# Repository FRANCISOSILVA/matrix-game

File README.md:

# Matrix-Game

Copyright (C) 2025 GWF AG, Obergrundstrasse 119, 6002 Lucerne, Switzerland

Contact: info@gwf.ch

## Trial Apprenticeship

This PCB is used as part of the trial apprenticeship for electronics/firmware at GWF AG in Lucerne.

_Deutsch: Schnupperlehre Elektroniker/in EFZ_

## Project

The project is used to practice soldering, measuring and potentially some coding.

The firmware currently supports the following games:
- [x] Snake
- [x] Tic-Tac-Toe

Feel free to submit a Pull Request to add more games! :tada:

## Changelogs

The changelogs can be find in the corresponding subdirectories:
- [Firmware Changelog](firmware/CHANGELOG.md)
- [Hardware Changelog](hardware/CHANGELOG.md)

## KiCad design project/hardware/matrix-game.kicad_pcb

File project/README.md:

# Project: Matrix-Game

This PCB is used as part of the trial apprenticeship to practice soldering, measuring and potentially some coding.

The firmware currently supports the following games:
- [x] Snake
- [x] Tic-Tac-Toe

Feel free to submit a Pull Request to add more games! :tada:

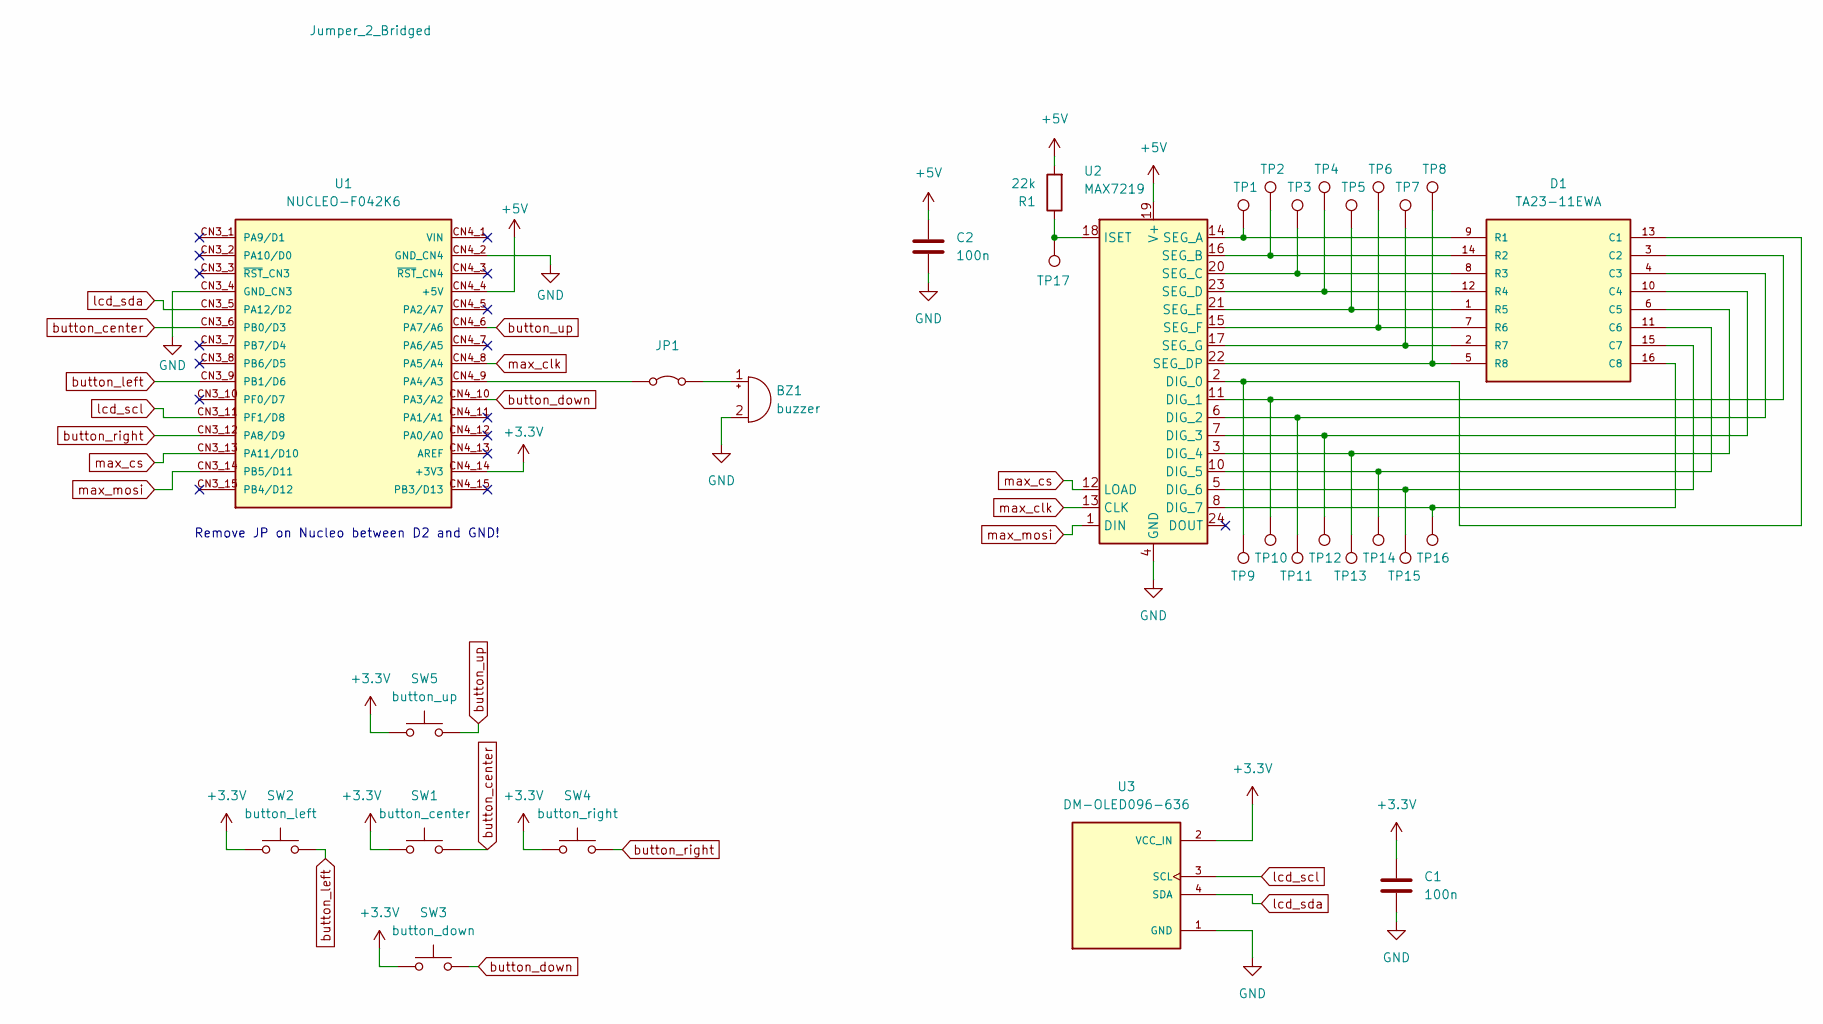
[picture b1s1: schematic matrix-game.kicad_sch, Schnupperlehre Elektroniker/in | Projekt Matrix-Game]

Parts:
BZ1: buzzer; Buzzer_12x9.5RM7.6
C1, C2: 100n; C_Disc_D3.0mm_W2.0mm_P2.50mm
D1: TA23-11EWA; LED_TA23-11EWA; PARTREV V.10A
JP1: Jumper_2_Bridged; PinHeader_1x02_P2.54mm_Vertical
R1: 22k; R_Axial_DIN0207_L6.3mm_D2.5mm_P10.16mm_Horizontal
SW1: button_center; SW_PUSH_6mm
SW2: button_left; SW_PUSH_6mm
SW3: button_down; SW_PUSH_6mm
SW4: button_right; SW_PUSH_6mm
SW5: button_up; SW_PUSH_6mm
TP1, TP2, TP3, TP4, TP5, TP6, TP7, TP8, TP9, TP10, TP11, TP12, TP13, TP14, TP15, TP16, TP17: TestPoint; PinHeader_1x01_P2.54mm_Vertical
U1: NUCLEO-F042K6; MODULE_NUCLEO-F042K6; PARTREV 8
U2: MAX7219; DIP-24_W7.62mm_Socket
U3: DM-OLED096-636; MODULE_DM-OLED096-636; PARTREV 2018-09-10

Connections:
+3.3V: C1.1, SW1.1, SW2.1, SW3.1, SW4.1, SW5.1, U1.CN4_14 (+3V3), U3.2 (VCC_IN)
+5V: C2.1, R1.2, U1.CN4_4 (+5V), U2.19 (V+)
GND: BZ1.2 (-), C1.2, C2.2, U1.CN3_4 (GND_CN3), U1.CN4_2 (GND_CN4), U2.4 (GND), U2.9 (GND), U3.1 (GND)
unnamed: BZ1.1 (+), JP1.2 (B)
unnamed: D1.13 (C1), TP9.1, U2.2 (DIG_0)
unnamed: D1.3 (C2), TP10.1, U2.11 (DIG_1)
unnamed: D1.4 (C3), TP11.1, U2.6 (DIG_2)
unnamed: D1.10 (C4), TP12.1, U2.7 (DIG_3)
unnamed: D1.6 (C5), TP13.1, U2.3 (DIG_4)
unnamed: D1.11 (C6), TP14.1, U2.10 (DIG_5)
unnamed: D1.15 (C7), TP15.1, U2.5 (DIG_6)
unnamed: D1.16 (C8), TP16.1, U2.8 (DIG_7)
unnamed: D1.9 (R1), TP1.1, U2.14 (SEG_A)
unnamed: D1.14 (R2), TP2.1, U2.16 (SEG_B)
unnamed: D1.8 (R3), TP3.1, U2.20 (SEG_C)
unnamed: D1.12 (R4), TP4.1, U2.23 (SEG_D)
unnamed: D1.1 (R5), TP5.1, U2.21 (SEG_E)
unnamed: D1.7 (R6), TP6.1, U2.15 (SEG_F)
unnamed: D1.2 (R7), TP7.1, U2.17 (SEG_G)
unnamed: D1.5 (R8), TP8.1, U2.22 (SEG_DP)
unnamed: JP1.1 (A), U1.CN4_9 (PA4/A3)
unnamed: R1.1, TP17.1, U2.18 (ISET)
button_center: SW1.2, U1.CN3_6 (PB0/D3)
button_down: SW3.2, U1.CN4_10 (PA3/A2)
button_left: SW2.2, U1.CN3_9 (PB1/D6)
button_right: SW4.2, U1.CN3_12 (PA8/D9)
button_up: SW5.2, U1.CN4_6 (PA7/A6)
lcd_scl: U1.CN3_11 (PF1/D8), U3.3 (SCL)
lcd_sda: U1.CN3_5 (PA12/D2), U3.4 (SDA)
max_clk: U1.CN4_8 (PA5/A4), U2.13 (CLK)
max_cs: U1.CN3_13 (PA11/D10), U2.12 (LOAD)
max_mosi: U1.CN3_14 (PB5/D11), U2.1 (DIN)

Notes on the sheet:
Remove JP on Nucleo between D2 and GND!

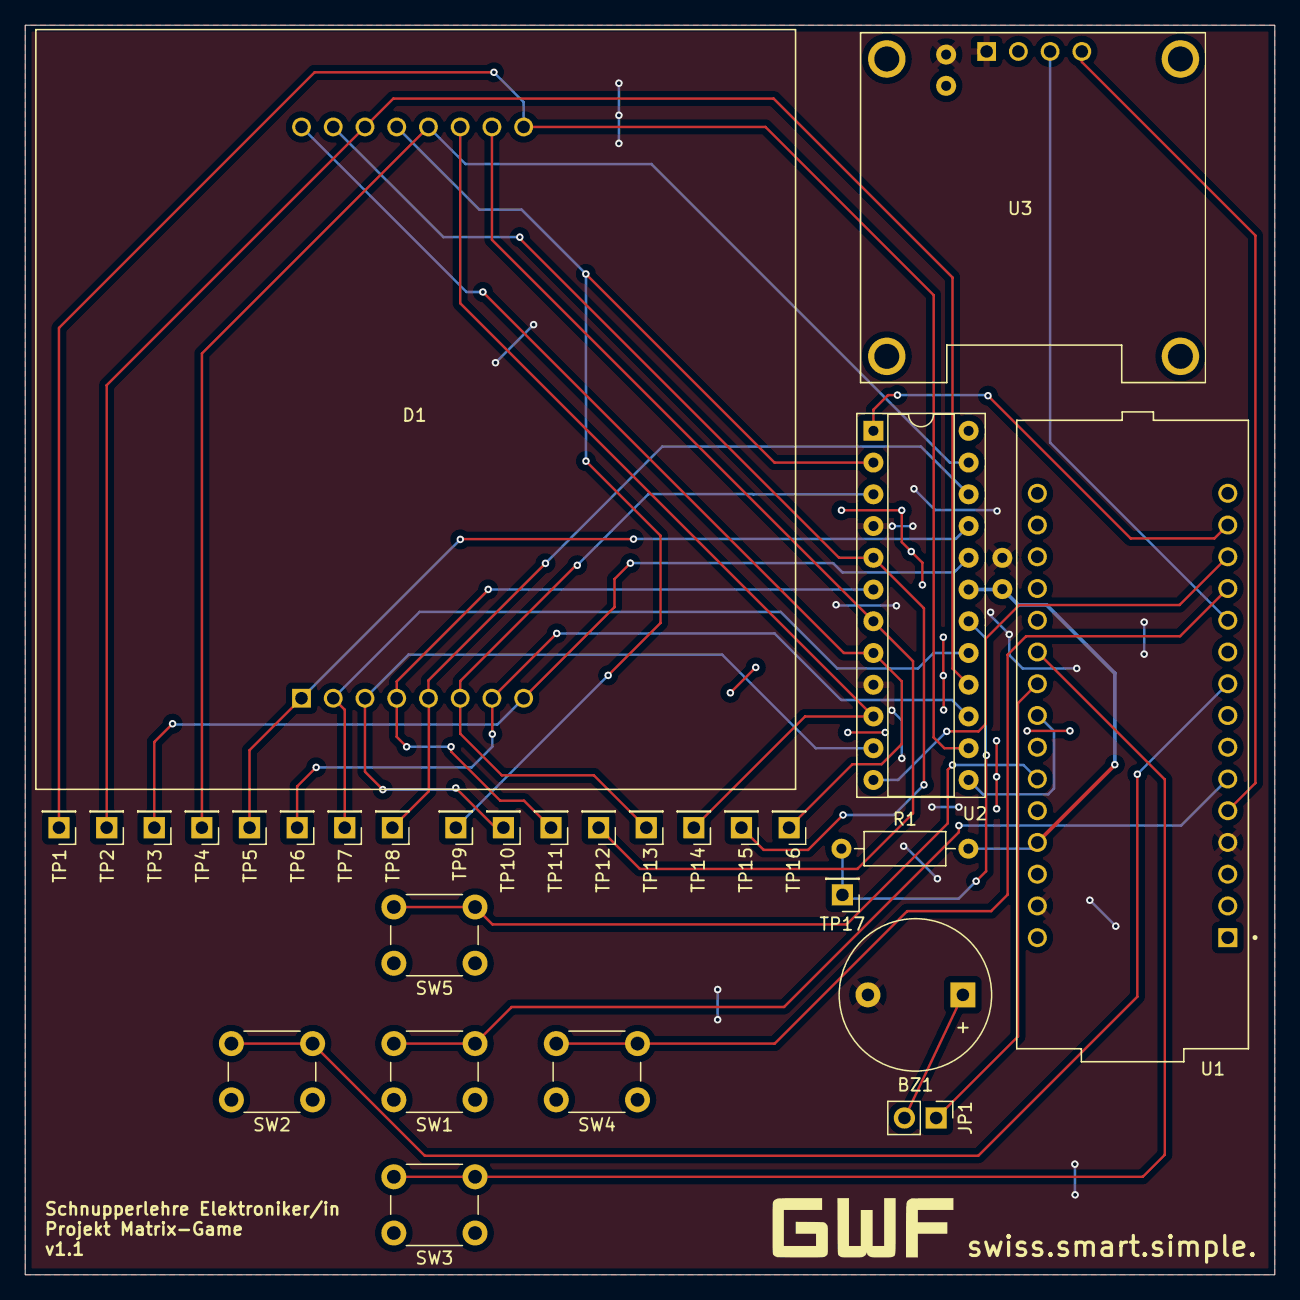
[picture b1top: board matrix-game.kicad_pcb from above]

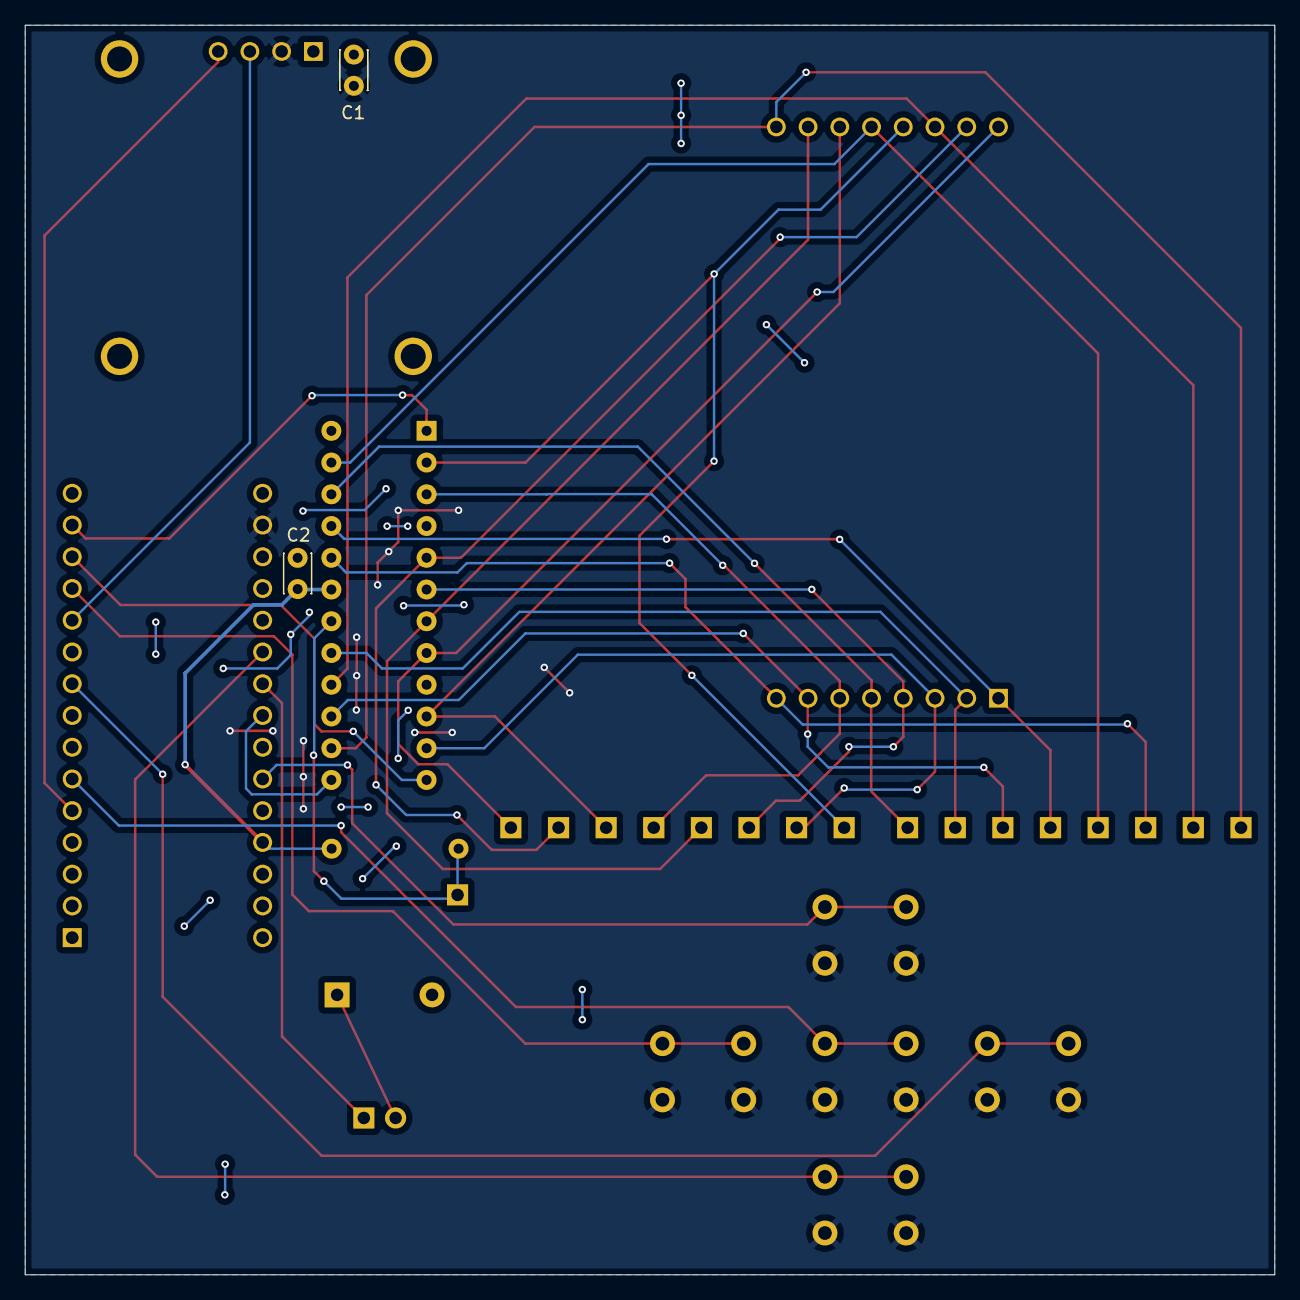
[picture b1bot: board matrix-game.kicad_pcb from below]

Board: 2 copper layers, 100.0 x 100.0 mm, 31 parts (2 on the bottom side), 32 nets.

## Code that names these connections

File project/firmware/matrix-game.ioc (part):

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Mcu.Name=STM32F042K(4-6)Tx
Mcu.Package=LQFP32
Mcu.UserName=STM32F042K6Tx
PA11.GPIOParameters=PinState,GPIO_Label
PA11.GPIO_Label=MAX_SPI_CS
PA11.PinState=GPIO_PIN_SET
PA11.Signal=GPIO_Output
PA12.GPIOParameters=GPIO_Label
PA12.GPIO_Label=LCD_I2C_SDA
PA12.Mode=I2C
PA12.Signal=I2C1_SDA
PA13.GPIOParameters=GPIO_Label
PA13.GPIO_Label=SWDIO
PA13.Mode=Serial_Wire
PA13.Signal=SYS_SWDIO
PA14.GPIOParameters=GPIO_Label
PA14.GPIO_Label=SWCLK
PA14.Mode=Serial_Wire
PA14.Signal=SYS_SWCLK
PA15.GPIOParameters=GPIO_Label
PA15.GPIO_Label=VCP_RX
PA15.Mode=Asynchronous
PA15.Signal=USART2_RX
PA2.GPIOParameters=GPIO_Label
PA2.GPIO_Label=VCP_TX
PA2.Mode=Asynchronous
PA2.Signal=USART2_TX
PA3.GPIOParameters=GPIO_PuPd,GPIO_Label
PA3.GPIO_Label=BUTTON_DOWN
PA3.GPIO_PuPd=GPIO_PULLDOWN
PA3.Signal=GPIO_Input
PA4.GPIOParameters=GPIO_Label
PA4.GPIO_Label=BUZZER
PA4.Signal=GPIO_Output
PA5.GPIOParameters=GPIO_Label
PA5.GPIO_Label=MAX_SPI_SCK
PA5.Mode=TX_Only_Simplex_Unidirect_Master
PA5.Signal=SPI1_SCK
PA7.GPIOParameters=GPIO_PuPd,GPIO_Label
PA7.GPIO_Label=BUTTON_UP
PA7.GPIO_PuPd=GPIO_PULLDOWN
PA7.Signal=GPIO_Input
PA8.GPIOParameters=GPIO_PuPd,GPIO_Label
PA8.GPIO_Label=BUTTON_RIGHT
PA8.GPIO_PuPd=GPIO_PULLDOWN
PA8.Signal=GPIO_Input
PB0.GPIOParameters=GPIO_PuPd,GPIO_Label
PB0.GPIO_Label=BUTTON_CENTER
PB0.GPIO_PuPd=GPIO_PULLDOWN
PB0.Signal=GPIO_Input
PB1.GPIOParameters=GPIO_PuPd,GPIO_Label
PB1.GPIO_Label=BUTTON_LEFT
PB1.GPIO_PuPd=GPIO_PULLDOWN
PB1.Signal=GPIO_Input
PB3.GPIOParameters=GPIO_Label
PB3.GPIO_Label=LED_GREEN
PB3.Signal=GPIO_Output
PB5.GPIOParameters=GPIO_Label
PB5.GPIO_Label=MAX_SPI_MOSI
PB5.Mode=TX_Only_Simplex_Unidirect_Master
PB5.Signal=SPI1_MOSI
PF0-OSC_IN.GPIOParameters=GPIO_Label
PF0-OSC_IN.GPIO_Label=MCO
PF0-OSC_IN.Mode=HSE-External-Clock-Source
PF0-OSC_IN.Signal=RCC_OSC_IN
PF1-OSC_OUT.GPIOParameters=GPIO_Label
PF1-OSC_OUT.GPIO_Label=LCD_I2C_SCL
PF1-OSC_OUT.Mode=I2C
PF1-OSC_OUT.Signal=I2C1_SCL
board=NUCLEO-F042K6
boardIOC=true

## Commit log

2025-02-05 Added README.md
2025-02-05 [general] updated README
2025-02-05 [project/firmware] initial commit with default MX configuration
2025-02-05 [project/firmware/minor] fix warning: elf has a LOAD segment with RWX permissions
2025-02-05 [project/firmware] initial config for LCD I2C
2025-02-05 [project/firmware] add app structure
    Everything that we implement will be part of (resp. called from) `app`.
    This helps to separate it from MX generated stuff within `main`.
2025-02-05 [project/firmware/lcd] added driver for LCD
    Source: https://controllerstech.com/oled-display-using-i2c-stm32/
2025-02-05 [project/firmware/lcd] added example how to use LCD driver
2025-02-05 [project/firmware/max] initial config for MAX7219 SPI
2025-02-05 [project/firmware/led] added user led LD3
    Not to forget that this GPIO is connected to the green Nucleo user led LD3.
2025-02-05 [project/firmware/buzzer] added buzzer
2025-02-05 [project/firmware/buttons] added buttons
2025-02-07 [project/hardware] initial commit of empty KiCad project
2025-02-07 [project/hardware/schematic] added max7219 and led matrix
2025-02-07 [project/hardware/schematic] added nucleo board and buttons
2025-02-07 [project/hardware/layout] added custom footprint for LCD
2025-02-07 [project/hardware/layout] rotation of matrix LED
2025-02-07 [project/hardware/schematic] added custom symbol for LCD, assigned footprints
2025-02-07 [project/hardware/layout] started layouting
2025-02-07 [project/hardware/schematic] added LCD
2025-02-07 [project/hardware/layout] set all tracks to 0.2 mm width
2025-02-07 [project/hardware] added test points
2025-02-07 [project/hardware] added capacitors for LCD and MAX7219, logo and version
2025-02-07 [project/hardware/layout] more layouting
2025-02-07 [project/hardware] added page settings
2025-02-07 [project/hardware] added jumper for buzzer
2025-02-07 [project/hardware/layout] turned TP labels to be better readable
2025-02-07 [project/hardware/schematic] added labels
2025-02-07 [project/hardware/layout] make 5V trace a bit thicker
2025-02-07 [project/hardware/layout] gerber settings
2025-02-07 [project/hardware/3d] added STEP for Nucleo and matrix LED
2025-02-07 [project/hardware] added library model for LCD, added sockets for Nucleo and LCD
2025-02-07 [project/hardware/3d] added 3D models for MA7219 and jumper
2025-02-07 [project] added README
2025-02-10 [project/hardware/schematic/minor] remove duplicated connection
2025-02-10 [project/hardware/layout] added page setup
2025-02-17 [project/firmware/gpio] default pin state for CS should be High
2025-02-17 [project/firmware/minor] added clang-format
2025-02-17 [project/firmware/max] added driver for MAX7219
    This is the multiplexer / LED driver for the LED matrix.
2025-02-17 [project/firmware] added examples for max7219 driver usage
2025-02-17 [project/firmware] refactoring: max7219_init() should also apply default configuration
    And also added a dedicated function to clear the matrix LED.
2025-02-18 [project/firmware] added snake game
2025-02-18 [project/firmware] refactoring: put snake game into dedicated file
    - app: handles general stuff that can be reused in the future for other games
    - snake: handles snake game specific stuff
2025-02-18 [project/firmware/minor] rename lcd folder
    Lets follow the convention to have user directories in lower case.
2025-02-18 [project/firmware] fix: do not abort game if CENTER button is pressed
    Previously the game was terminated by `snake_move()` when CENTER button
    was pressed.
    Now, the CENTER button is simply ignored while playing the snake game.
2025-02-24 [project/hardware] changed value of R1
2025-02-24 [project/hardware] fix: wrong connection of R1
    R1 was wrongly connectet to GND instead of +5V
2025-02-24 [project/hardware] added text: Remove JP on Nucleo between D2 and GND!
2025-02-24 [project/general] updated README
2025-02-24 [project/hardware] fix: footprint of LCD
    Adjusted mouting hole distances:
    - previous[mm]: 22x22
    - now[mm]: 23.5x23.8
2025-02-24 [project/hardware] v1.1
2025-03-03 [project/firmware] move everything related to snake into snake module
    This is a preparation to be able to add more games in the future.
2025-03-03 [project/firmware] added TicTacToe game
    Previously, there was only the snake game.
    Now, the user can select between two games:
    - Snake
    - TicTacToe
2025-03-03 [project/firmware] v1.1
2025-03-03 [project/firmware/minor] LCD: add const qualifier
2025-03-04 [project/firmware] refactoring: make it easier to add new games in the future
    We now have a `games` array which holds all the info about the available
    games. This makes it easy to add new games in the future.
2025-03-04 [project/firmware] game selection: improve user experience for scrolling
    We should only change the game options that we show on the screen if
    we really need to. If the new cursor position is still within the
    previous screen, we should not move the options on the screen but
    only the cursor.
2025-03-04 [project/firmware] game selection: improve user experience for selection
    Remember what game the user played last and put this as default for the next selection
2025-03-04 [project/firmware] v1.2
2025-03-04 [project] updated README
2025-03-10 [general] move project structure one level up
    Initially, the idea was to have multiple things about the trial
    apprenticeship in this repo, the matrix-game project being one of them.
    Now, we use this repo only for the matrix-game, so lets move the files
    one level up.
2025-04-17 Add MIT license
2025-08-14 [firmware] new drawing game
2025-08-14 [firmware/docs] updated CHANGELOG
2025-08-14 [firmware] new BombDodging game
